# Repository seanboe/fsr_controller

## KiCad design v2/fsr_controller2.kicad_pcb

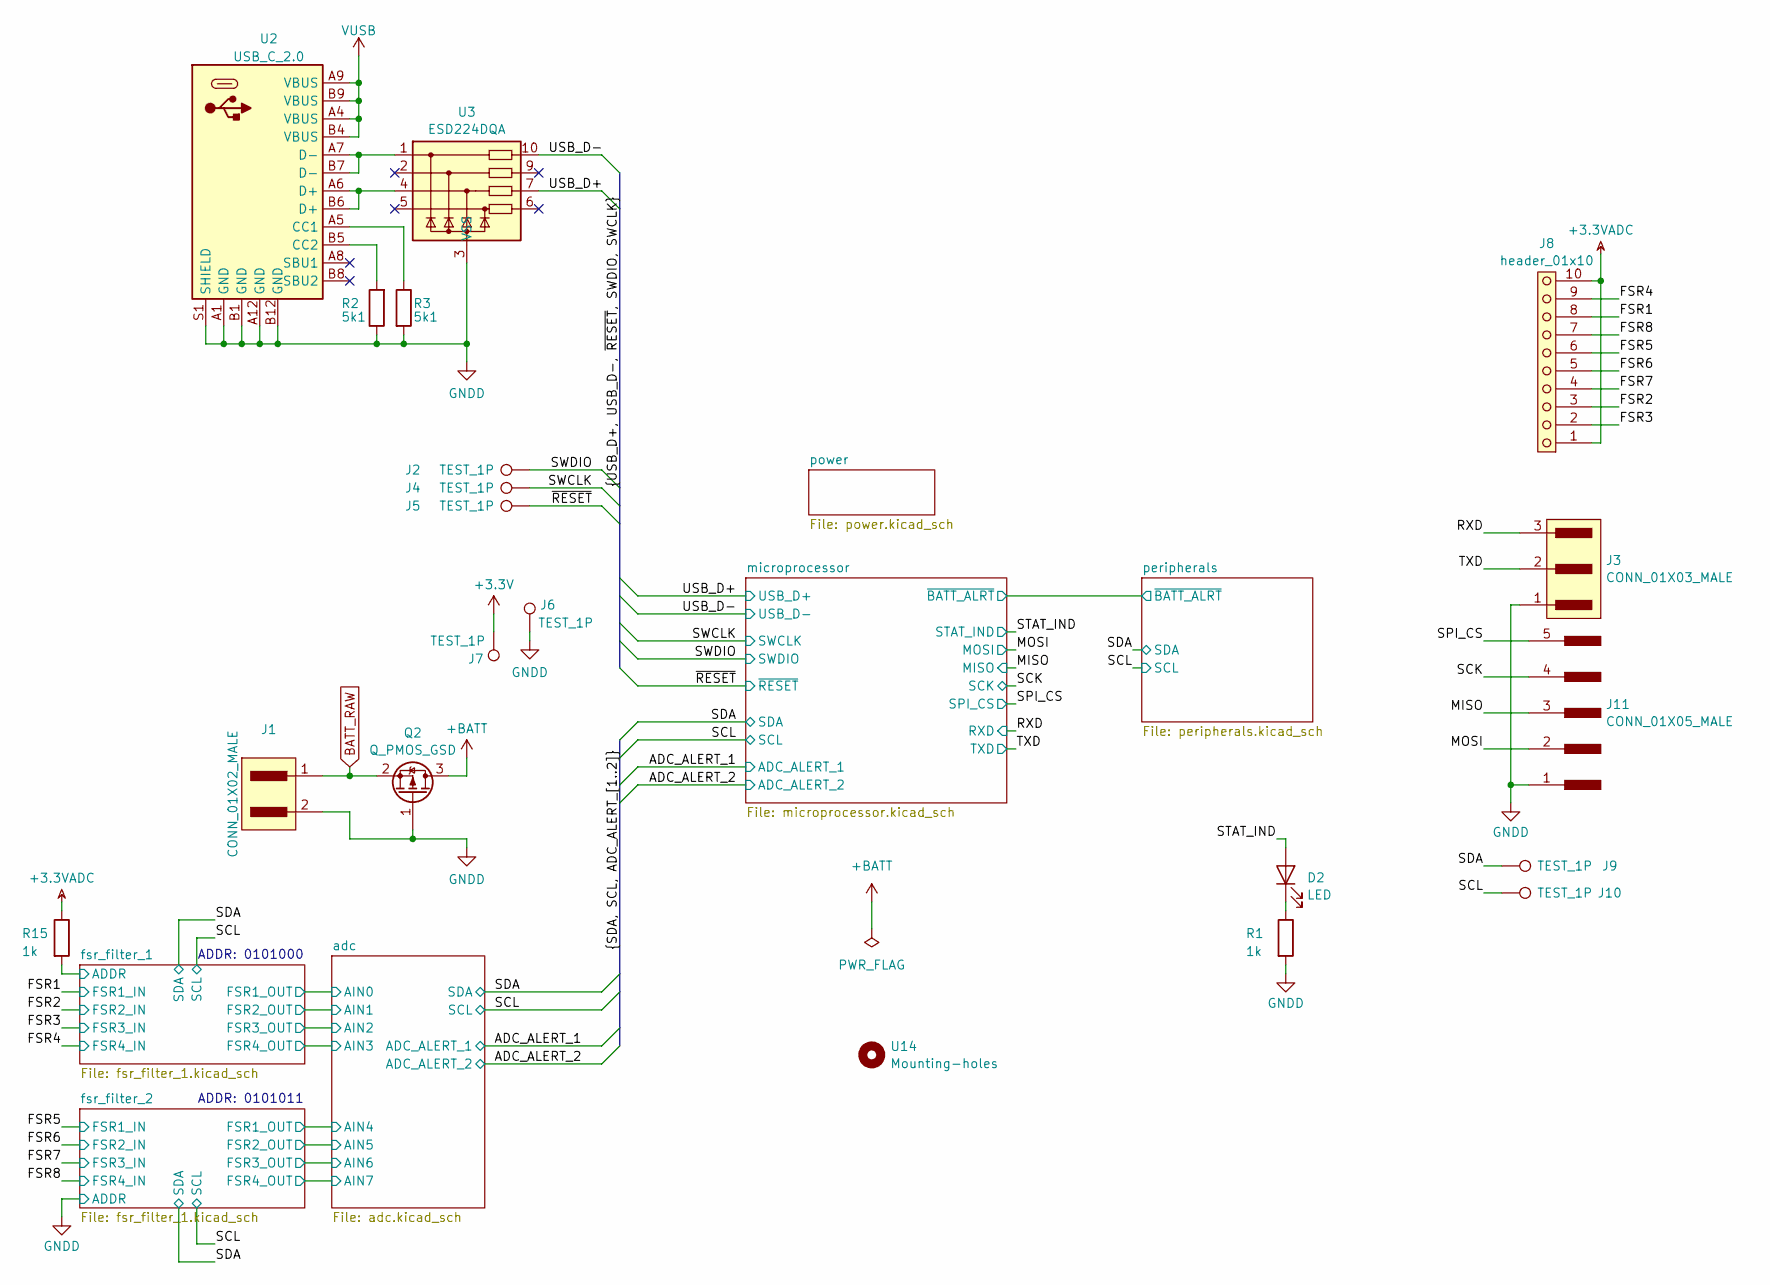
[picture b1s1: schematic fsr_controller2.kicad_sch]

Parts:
D2: LED; D_0603; MPN C94869
J1: CONN_01X02_MALE; JST_PH_S2B-PH-SM4-TB_1x02-1MP_P2.00mm_Horizontal; MPN C295747
J2, J4, J5, J6, J7, J9, J10: TEST_1P; test_point_1.0mm_square
J3: CONN_01X03_MALE; JST_BM03B_GHS_TB; MPN C514175
J8: header_01x10; fsr_connector
J11: CONN_01X05_MALE; JST_SM05B; MPN C189896
Q2: Q_PMOS_GSD; SOT-23; MPN C727156
R1, R15: 1k; R_1608_603_B; MPN C2984405
R2, R3: 5k1; R_1608_603_B; MPN C23186
U2: USB_C_2.0; USB_C_XKB_U262-16XN-4BVC11; MPN C165948
U3: ESD224DQA; Diodes_UDFN-10_1.0x2.5mm_P0.5mm
U14: Mounting-holes; plated_hole_2.0x2.5mm

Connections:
+3.3V: J7.1; also elsewhere on the board
+3.3VADC: J8.1, J8.10, R15.1; also elsewhere on the board
+BATT: Q2.3 (D); also elsewhere on the board
/FSR1: J8.8; also elsewhere on the board
/FSR2: J8.3; also elsewhere on the board
/FSR3: J8.2; also elsewhere on the board
/FSR4: J8.9; also elsewhere on the board
/FSR5: J8.6; also elsewhere on the board
/FSR6: J8.5; also elsewhere on the board
/FSR7: J8.4; also elsewhere on the board
/FSR8: J8.7; also elsewhere on the board
/MISO: J11.3; also elsewhere on the board
/MOSI: J11.2; also elsewhere on the board
/RXD: J3.3; also elsewhere on the board
/SCK: J11.4; also elsewhere on the board
/SCL: J10.1; also elsewhere on the board
/SDA: J9.1; also elsewhere on the board
/SPI_CS: J11.5; also elsewhere on the board
/STAT_IND: D2.2 (A); also elsewhere on the board
/SWCLK: J4.1; also elsewhere on the board
/SWDIO: J2.1; also elsewhere on the board
/TXD: J3.2; also elsewhere on the board
/USB_D+: U3.7; also elsewhere on the board
/USB_D-: U3.10; also elsewhere on the board
/fsr_filter_1/ADDR: R15.2; also elsewhere on the board
/~RESET: J5.1; also elsewhere on the board
BATT_RAW: J1.1, Q2.2 (S); also elsewhere on the board
GNDD: J1.2, J3.1, J6.1, J11.1, Q2.1 (G), R1.2, R2.1, R3.2, U2.A1 (GND), U2.A12 (GND), U2.B1 (GND), U2.B12 (GND), U2.S1 (SHIELD), U3.3 (VSS), U3.8 (VSS); also elsewhere on the board
unnamed: D2.1 (K), R1.1
unnamed: R3.1, U2.A5 (CC1)
unnamed: R2.2, U2.B5 (CC2)
unnamed: U2.A6 (D+), U2.B6 (D+), U3.4
unnamed: U2.A7 (D-), U2.B7 (D-), U3.1
VUSB: U2.A4 (VBUS), U2.A9 (VBUS), U2.B4 (VBUS), U2.B9 (VBUS); also elsewhere on the board

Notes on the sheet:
ADDR: 0101011
ADDR: 0101000

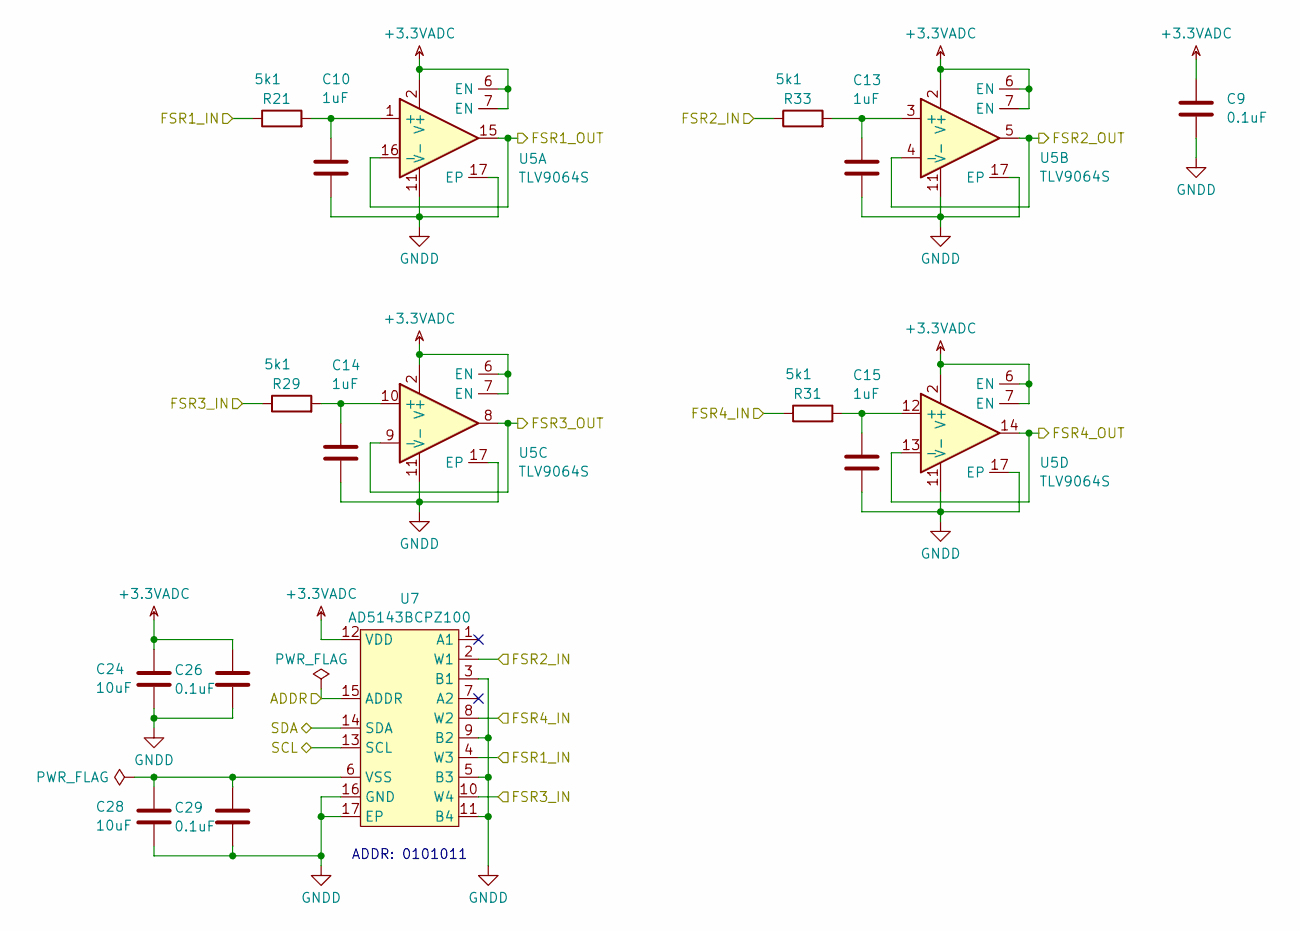
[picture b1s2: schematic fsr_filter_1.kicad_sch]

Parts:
C9, C26, C29: 0.1uF; C_1608_603_B; MPN C2909630
C10, C13, C14, C15: 1uF; C_1608_603_B; MPN C2918499
C24, C28: 10uF; C_1608_603_B; MPN C2909630
R21, R29, R31, R33: 5k1; R_1608_603_B; MPN C23186
U5: TLV9064S; WQFN-16-1EP_3x3mm_P0.5mm_EP1.68x1.68mm; MPN DIGI
U7: AD5143BCPZ100; WQFN-16-1EP_3x3mm_P0.5mm_EP1.68x1.68mm

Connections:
+3.3VADC: C9.1, C24.1, C26.1, U5.2 (V+), U5.6 (EN), U5.7 (EN), U7.12 (VDD); also elsewhere on the board
/FSR1: R21.1, U7.4 (W3); also elsewhere on the board
/FSR2: R33.1, U7.2 (W1); also elsewhere on the board
/FSR3: R29.1, U7.10 (W4); also elsewhere on the board
/FSR4: R31.1, U7.8 (W2); also elsewhere on the board
/SCL: U7.13 (SCL); also elsewhere on the board
/SDA: U7.14 (SDA); also elsewhere on the board
/adc/AIN0: U5.15, U5.16 (-); also elsewhere on the board
/adc/AIN1: U5.4 (-), U5.5; also elsewhere on the board
/adc/AIN2: U5.8, U5.9 (-); also elsewhere on the board
/adc/AIN3: U5.13 (-), U5.14; also elsewhere on the board
/fsr_filter_1/ADDR: U7.15 (ADDR); also elsewhere on the board
GNDD: C9.2, C10.2, C13.2, C14.2, C15.2, C24.2, C26.2, C28.2, C29.2, U5.11 (V-), U5.17 (EP), U7.3 (B1), U7.5 (B3), U7.9 (B2), U7.11 (B4), U7.16 (GND), U7.17 (EP); also elsewhere on the board
unnamed: C10.1, R21.2, U5.1 (+)
unnamed: C13.1, R33.2, U5.3 (+)
unnamed: C14.1, R29.2, U5.10 (+)
unnamed: C15.1, R31.2, U5.12 (+)
unnamed: C28.1, C29.1, U7.6 (VSS)

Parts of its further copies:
C3, C4: 10uF; C_1608_603_B; MPN C2909630
C12, C16, C25: 0.1uF; C_1608_603_B; MPN C2909630
C17, C18, C19, C22: 1uF; C_1608_603_B; MPN C2918499
R11, R12, R13, R14: 5k1; R_1608_603_B; MPN C23186
U12: TLV9064S; WQFN-16-1EP_3x3mm_P0.5mm_EP1.68x1.68mm; MPN DIGI
U13: AD5143BCPZ100; WQFN-16-1EP_3x3mm_P0.5mm_EP1.68x1.68mm

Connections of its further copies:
+3.3VADC: C3.1, C12.1, C25.1, U12.2 (V+), U12.6 (EN), U12.7 (EN), U13.12 (VDD); also elsewhere on the board
/FSR5: R11.1, U13.4 (W3); also elsewhere on the board
/FSR6: R13.1, U13.2 (W1); also elsewhere on the board
/FSR7: R12.1, U13.10 (W4); also elsewhere on the board
/FSR8: R14.1, U13.8 (W2); also elsewhere on the board
/SCL: U13.13 (SCL); also elsewhere on the board
/SDA: U13.14 (SDA); also elsewhere on the board
/adc/AIN4: U12.15, U12.16 (-); also elsewhere on the board
/adc/AIN5: U12.4 (-), U12.5; also elsewhere on the board
/adc/AIN6: U12.8, U12.9 (-); also elsewhere on the board
/adc/AIN7: U12.13 (-), U12.14; also elsewhere on the board
GNDD: C3.2, C4.2, C12.2, C16.2, C17.2, C18.2, C19.2, C22.2, C25.2, U12.11 (V-), U12.17 (EP), U13.3 (B1), U13.5 (B3), U13.9 (B2), U13.11 (B4), U13.15 (ADDR), U13.16 (GND), U13.17 (EP); also elsewhere on the board
unnamed: C17.1, R11.2, U12.1 (+)
unnamed: C19.1, R13.2, U12.3 (+)
unnamed: C18.1, R12.2, U12.10 (+)
unnamed: C22.1, R14.2, U12.12 (+)
unnamed: C4.1, C16.1, U13.6 (VSS)

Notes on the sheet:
ADDR: 0101011

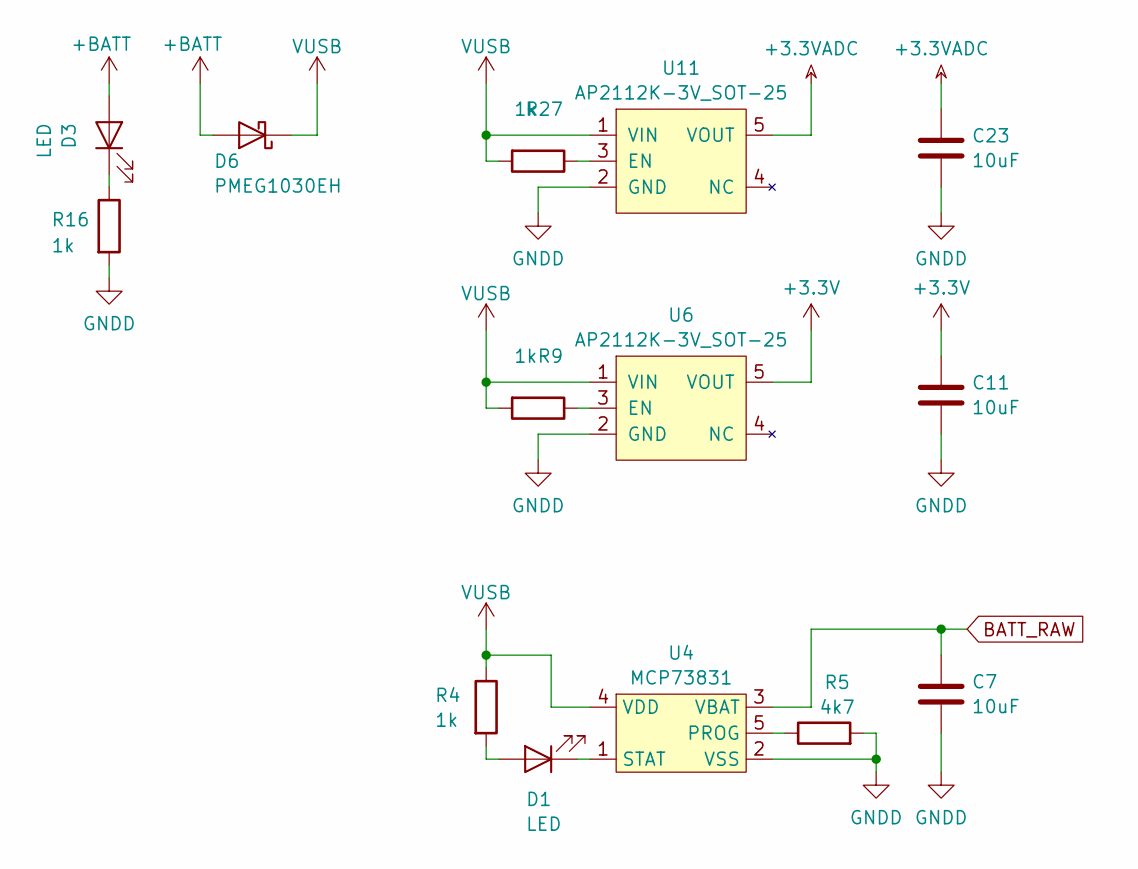
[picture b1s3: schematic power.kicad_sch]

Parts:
C7, C11, C23: 10uF; C_1608_603_B; MPN C2909630
D1, D3: LED; D_0603; MPN C94869
D6: PMEG1030EH; D_SOD-123F; MPN DIGI
R4, R9, R16, R27: 1k; R_1608_603_B; MPN C2984405
R5: 4k7; R_1608_603_B; MPN C2984421
U4: MCP73831; SOT-23-5; MPN C424093
U6, U11: AP2112K-3V_SOT-25; SOT-23-5; MPN C51118

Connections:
+3.3V: C11.1, U6.5 (VOUT); also elsewhere on the board
+3.3VADC: C23.1, U11.5 (VOUT); also elsewhere on the board
+BATT: D3.2 (A), D6.2 (A); also elsewhere on the board
BATT_RAW: C7.1, U4.3 (VBAT); also elsewhere on the board
GNDD: C7.2, C11.2, C23.2, R5.2, R16.2, U4.2 (VSS), U6.2 (GND), U11.2 (GND); also elsewhere on the board
unnamed: D1.2 (A), R4.2
unnamed: D1.1 (K), U4.1 (STAT)
unnamed: D3.1 (K), R16.1
unnamed: R5.1, U4.5 (PROG)
unnamed: R9.1, U6.3 (EN)
unnamed: R27.1, U11.3 (EN)
VUSB: D6.1 (K), R4.1, R9.2, R27.2, U4.4 (VDD), U6.1 (VIN), U11.1 (VIN); also elsewhere on the board

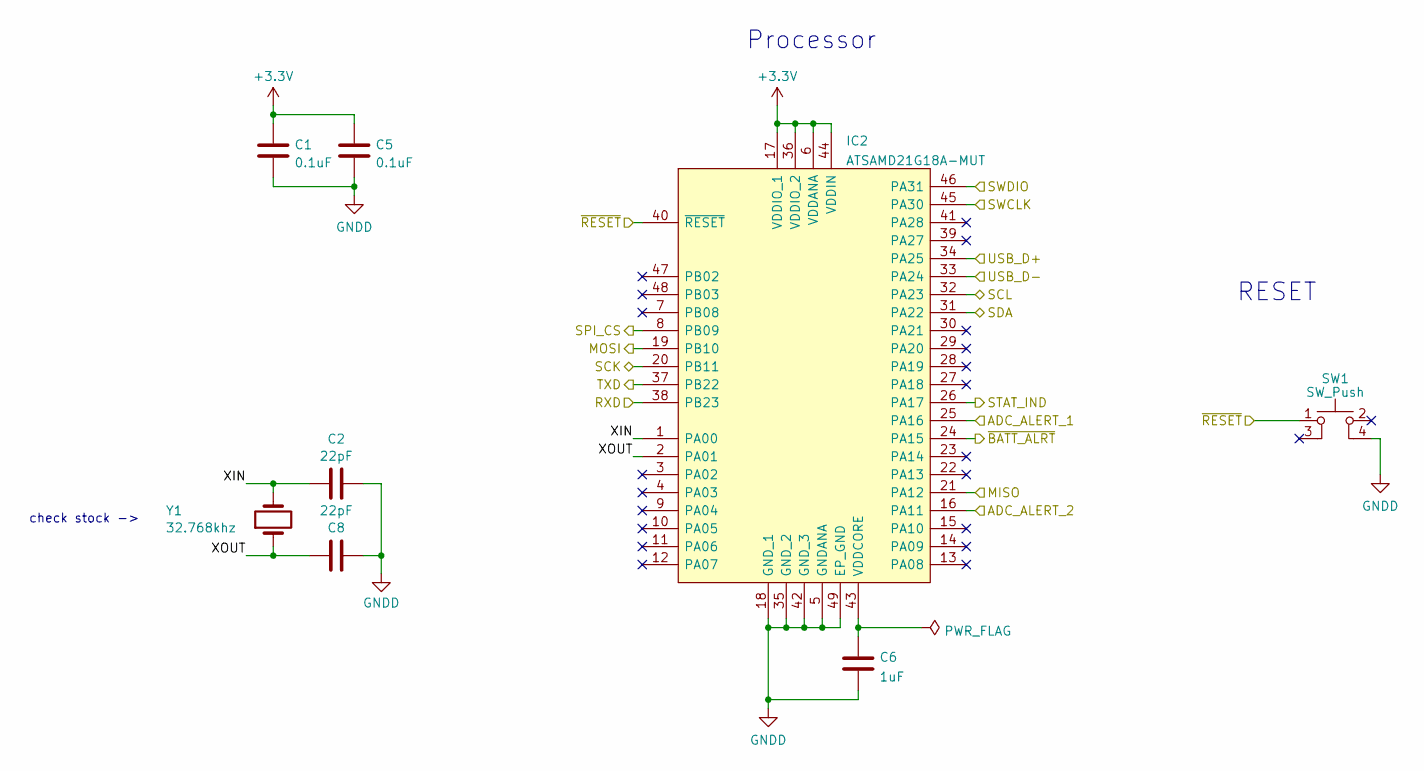
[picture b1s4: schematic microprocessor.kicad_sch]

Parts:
C1, C5: 0.1uF; C_1608_603_B; MPN C2909630
C2, C8: 22pF; C_1005_402_B; MPN C173271
C6: 1uF; C_1608_603_B; MPN C2918499
IC2: ATSAMD21G18A-MUT; QFN50P700X700X90-49N-D; MPN DIGI
SW1: SW_Push; TL3365AF180QG; MPN C2886926
Y1: 32.768khz; 2-smd

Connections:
+3.3V: C1.2, C5.2, IC2.6 (VDDANA), IC2.17 (VDDIO_1), IC2.36 (VDDIO_2), IC2.44 (VDDIN); also elsewhere on the board
/ADC_ALERT_1: IC2.25 (PA16); also elsewhere on the board
/ADC_ALERT_2: IC2.16 (PA11); also elsewhere on the board
/MISO: IC2.21 (PA12); also elsewhere on the board
/MOSI: IC2.19 (PB10); also elsewhere on the board
/RXD: IC2.38 (PB23); also elsewhere on the board
/SCK: IC2.20 (PB11); also elsewhere on the board
/SCL: IC2.32 (PA23); also elsewhere on the board
/SDA: IC2.31 (PA22); also elsewhere on the board
/SPI_CS: IC2.8 (PB09); also elsewhere on the board
/STAT_IND: IC2.26 (PA17); also elsewhere on the board
/SWCLK: IC2.45 (PA30); also elsewhere on the board
/SWDIO: IC2.46 (PA31); also elsewhere on the board
/TXD: IC2.37 (PB22); also elsewhere on the board
/USB_D+: IC2.34 (PA25); also elsewhere on the board
/USB_D-: IC2.33 (PA24); also elsewhere on the board
/microprocessor/XIN: C2.2, IC2.1 (PA00), Y1.2
/microprocessor/XOUT: C8.2, IC2.2 (PA01), Y1.1
/peripherals/~ALRT: IC2.24 (PA15); also elsewhere on the board
/~RESET: IC2.40 (~RESET), SW1.1; also elsewhere on the board
GNDD: C1.1, C2.1, C5.1, C6.2, C8.1, IC2.5 (GNDANA), IC2.18 (GND_1), IC2.35 (GND_2), IC2.42 (GND_3), IC2.49 (EP_GND), SW1.4; also elsewhere on the board
unnamed: C6.1, IC2.43 (VDDCORE)

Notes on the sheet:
check stock ->
RESET
Processor

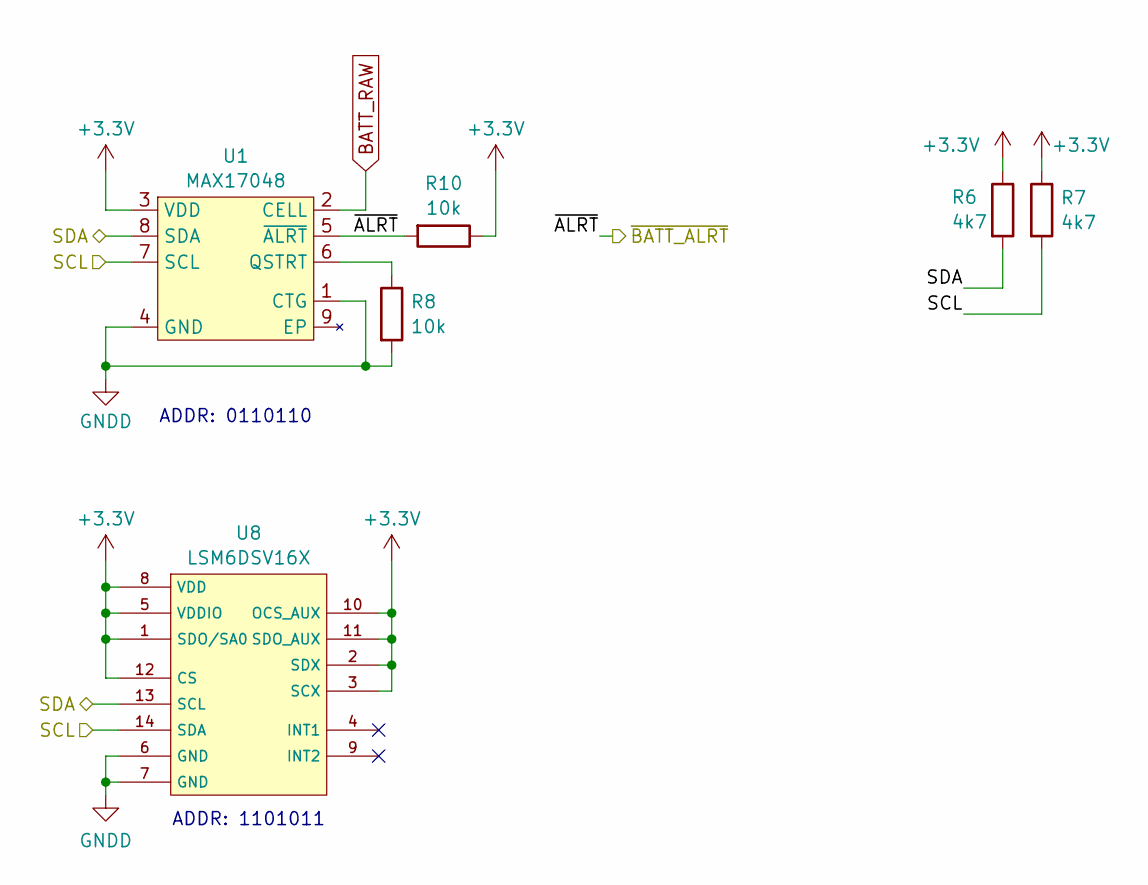
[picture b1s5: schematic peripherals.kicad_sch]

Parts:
R6, R7: 4k7; R_1608_603_B; MPN C2984421
R8, R10: 10k; R_1608_603_B; MPN C5123581
U1: MAX17048; DFN-8-1EP_2x2mm_P0.5mm_EP0.9x1.5mm; MPN C2682616
U8: LSM6DSV16X; PQFN50P250X300X86-14N; MPN DIGI

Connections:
+3.3V: R6.1, R7.1, R10.1, U1.3 (VDD), U8.1 (SDO/SA0), U8.2 (SDX), U8.3 (SCX), U8.5 (VDDIO), U8.8 (VDD), U8.10 (OCS_AUX), U8.11 (SDO_AUX), U8.12 (CS); also elsewhere on the board
/SCL: R7.2, U1.7 (SCL), U8.14 (SDA); also elsewhere on the board
/SDA: R6.2, U1.8 (SDA), U8.13 (SCL); also elsewhere on the board
/peripherals/~ALRT: R10.2, U1.5 (~ALRT); also elsewhere on the board
BATT_RAW: U1.2 (CELL); also elsewhere on the board
GNDD: R8.2, U1.1 (CTG), U1.4 (GND), U8.6 (GND), U8.7 (GND); also elsewhere on the board
unnamed: R8.1, U1.6 (QSTRT)

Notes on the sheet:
ADDR: 1101011
ADDR: 0110110

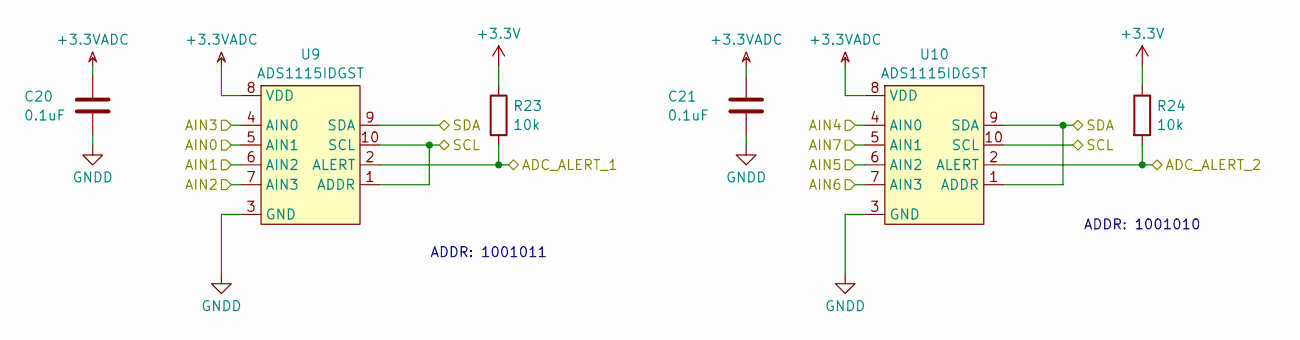
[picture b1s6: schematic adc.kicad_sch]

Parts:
C20, C21: 0.1uF; C_1608_603_B; MPN C2909630
R23, R24: 10k; R_1608_603_B; MPN C5123581
U9, U10: ADS1115IDGST; VSSOP-10_3x3mm_P0.5mm

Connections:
+3.3V: R23.1, R24.1; also elsewhere on the board
+3.3VADC: C20.1, C21.1, U9.8 (VDD), U10.8 (VDD); also elsewhere on the board
/ADC_ALERT_1: R23.2, U9.2 (ALERT); also elsewhere on the board
/ADC_ALERT_2: R24.2, U10.2 (ALERT); also elsewhere on the board
/SCL: U9.1 (ADDR), U9.10 (SCL), U10.10 (SCL); also elsewhere on the board
/SDA: U9.9 (SDA), U10.1 (ADDR), U10.9 (SDA); also elsewhere on the board
/adc/AIN0: U9.5 (AIN1); also elsewhere on the board
/adc/AIN1: U9.6 (AIN2); also elsewhere on the board
/adc/AIN2: U9.7 (AIN3); also elsewhere on the board
/adc/AIN3: U9.4 (AIN0); also elsewhere on the board
/adc/AIN4: U10.4 (AIN0); also elsewhere on the board
/adc/AIN5: U10.6 (AIN2); also elsewhere on the board
/adc/AIN6: U10.7 (AIN3); also elsewhere on the board
/adc/AIN7: U10.5 (AIN1); also elsewhere on the board
GNDD: C20.2, C21.2, U9.3 (GND), U10.3 (GND); also elsewhere on the board

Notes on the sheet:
ADDR: 1001010
ADDR: 1001011

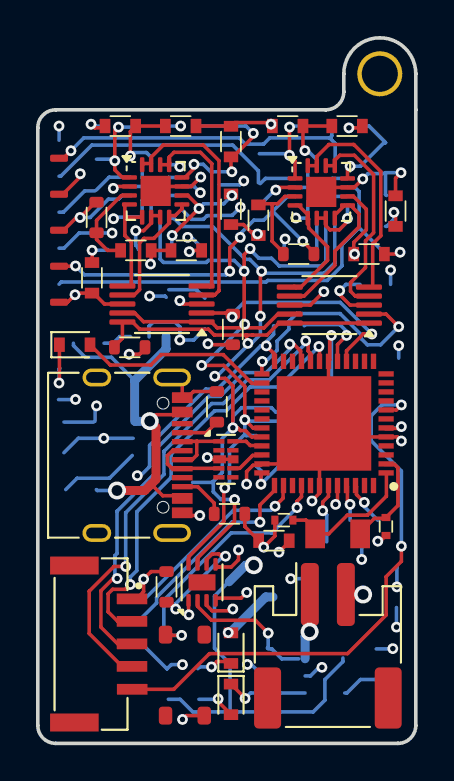
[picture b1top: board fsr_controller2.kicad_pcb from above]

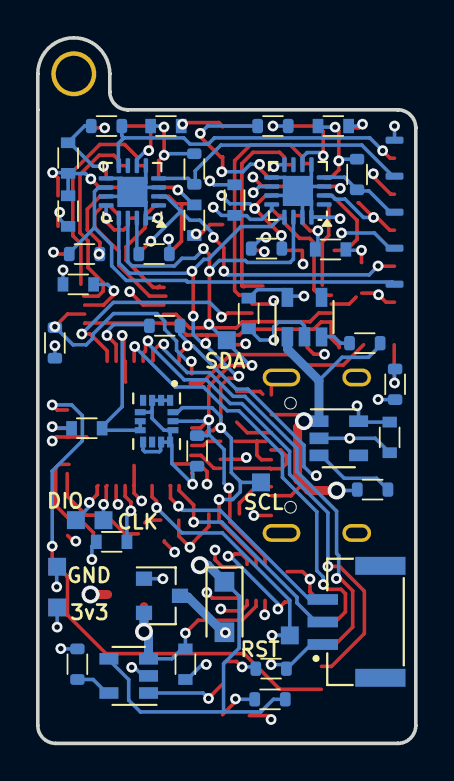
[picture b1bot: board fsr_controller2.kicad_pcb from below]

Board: 4 copper layers, 21.0 x 39.2 mm, 84 parts (45 on the bottom side), 65 nets.

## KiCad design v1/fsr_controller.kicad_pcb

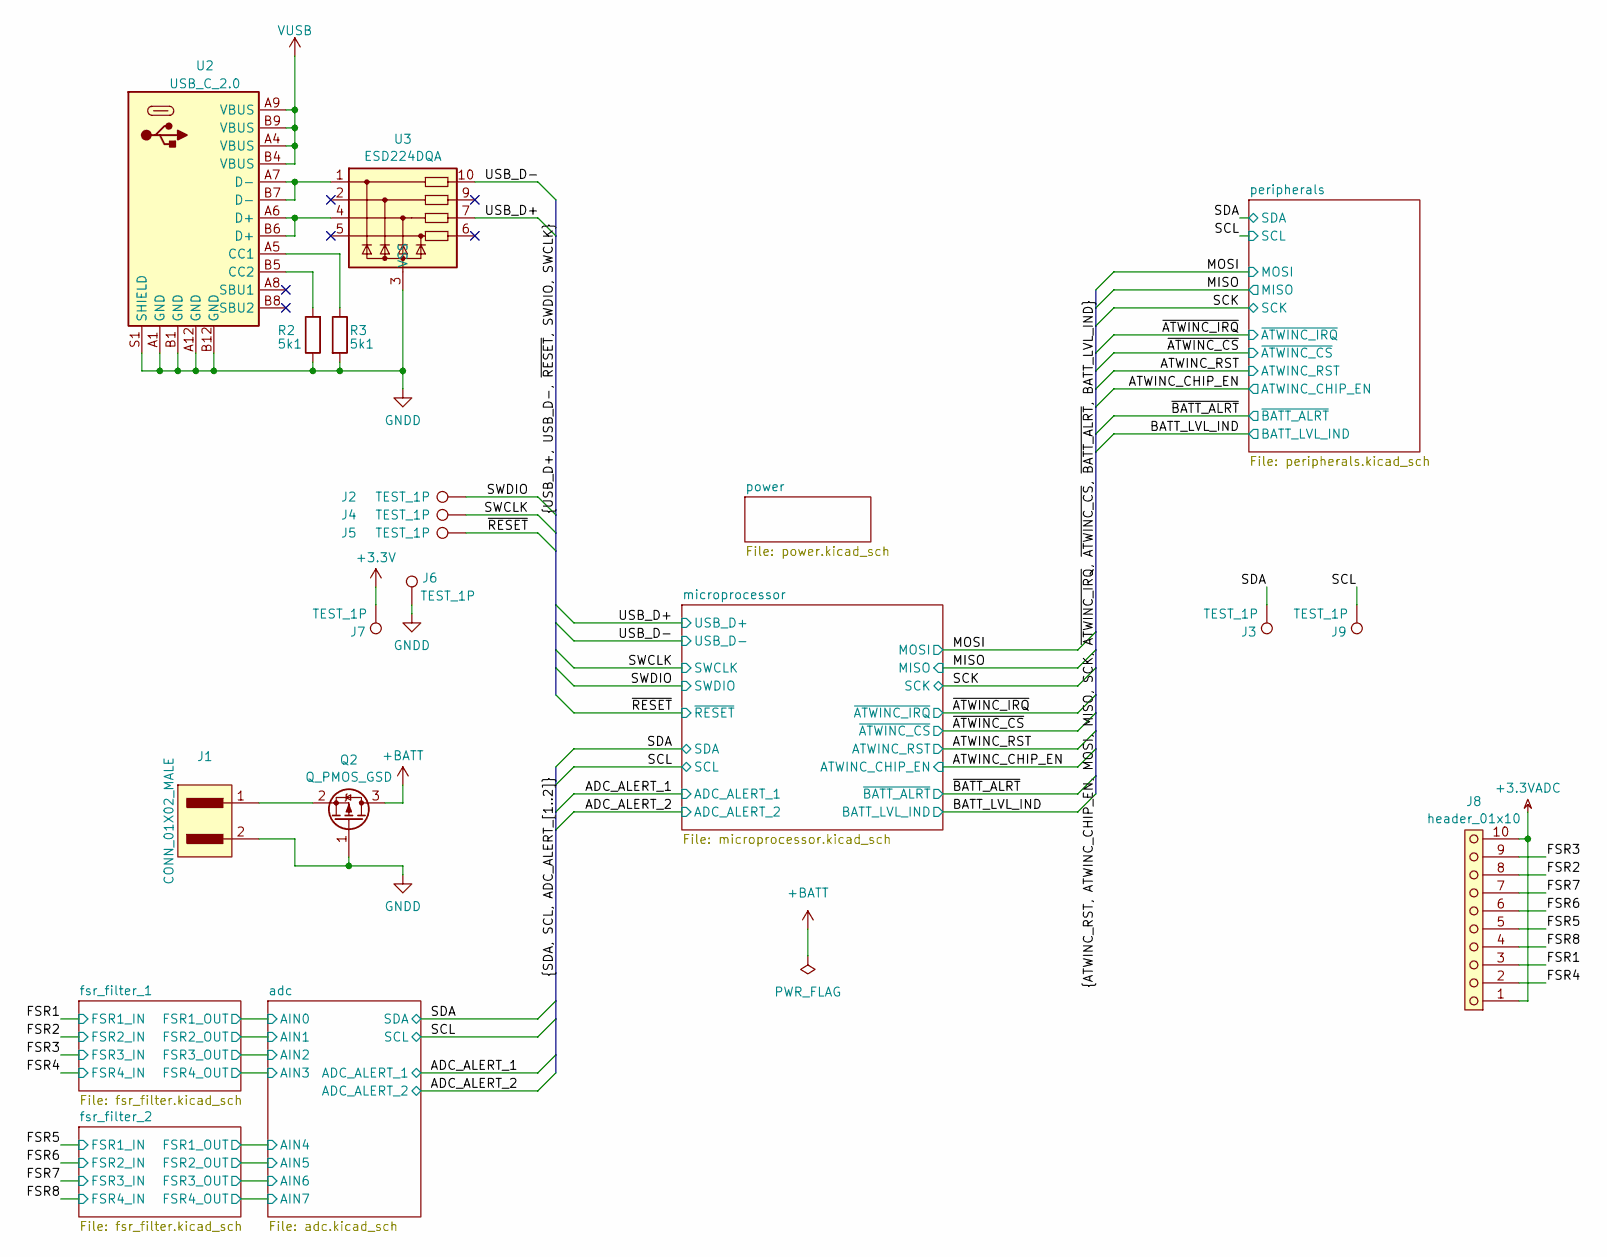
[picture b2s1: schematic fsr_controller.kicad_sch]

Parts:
J1: CONN_01X02_MALE; JST_PH_S2B-PH-SM4-TB_1x02-1MP_P2.00mm_Horizontal
J2, J3, J4, J5, J6, J7, J9: TEST_1P; test_point_1.0mm_square
J8: header_01x10; fsr_connector
Q2: Q_PMOS_GSD; SOT-23
R2, R3: 5k1; R_1608_603_B
U2: USB_C_2.0; USB_C_XKB_U262-16XN-4BVC11
U3: ESD224DQA; Diodes_UDFN-10_1.0x2.5mm_P0.5mm

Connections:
+3.3V: J7.1; also elsewhere on the board
+3.3VADC: J8.1, J8.10; also elsewhere on the board
+BATT: Q2.3 (D); also elsewhere on the board
/FSR1: J8.3; also elsewhere on the board
/FSR2: J8.8; also elsewhere on the board
/FSR3: J8.9; also elsewhere on the board
/FSR4: J8.2; also elsewhere on the board
/FSR5: J8.5; also elsewhere on the board
/FSR6: J8.6; also elsewhere on the board
/FSR7: J8.7; also elsewhere on the board
/FSR8: J8.4; also elsewhere on the board
/SCL: J9.1; also elsewhere on the board
/SDA: J3.1; also elsewhere on the board
/SWCLK: J4.1; also elsewhere on the board
/SWDIO: J2.1; also elsewhere on the board
/USB_D+: U3.7; also elsewhere on the board
/USB_D-: U3.10; also elsewhere on the board
/~RESET: J5.1; also elsewhere on the board
GNDD: J1.2, J6.1, Q2.1 (G), R2.1, R3.2, U2.A1 (GND), U2.A12 (GND), U2.B1 (GND), U2.B12 (GND), U2.S1 (SHIELD), U3.3 (VSS), U3.8 (VSS); also elsewhere on the board
unnamed: J1.1, Q2.2 (S)
unnamed: R3.1, U2.A5 (CC1)
unnamed: R2.2, U2.B5 (CC2)
unnamed: U2.A6 (D+), U2.B6 (D+), U3.4
unnamed: U2.A7 (D-), U2.B7 (D-), U3.1
VUSB: U2.A4 (VBUS), U2.A9 (VBUS), U2.B4 (VBUS), U2.B9 (VBUS); also elsewhere on the board

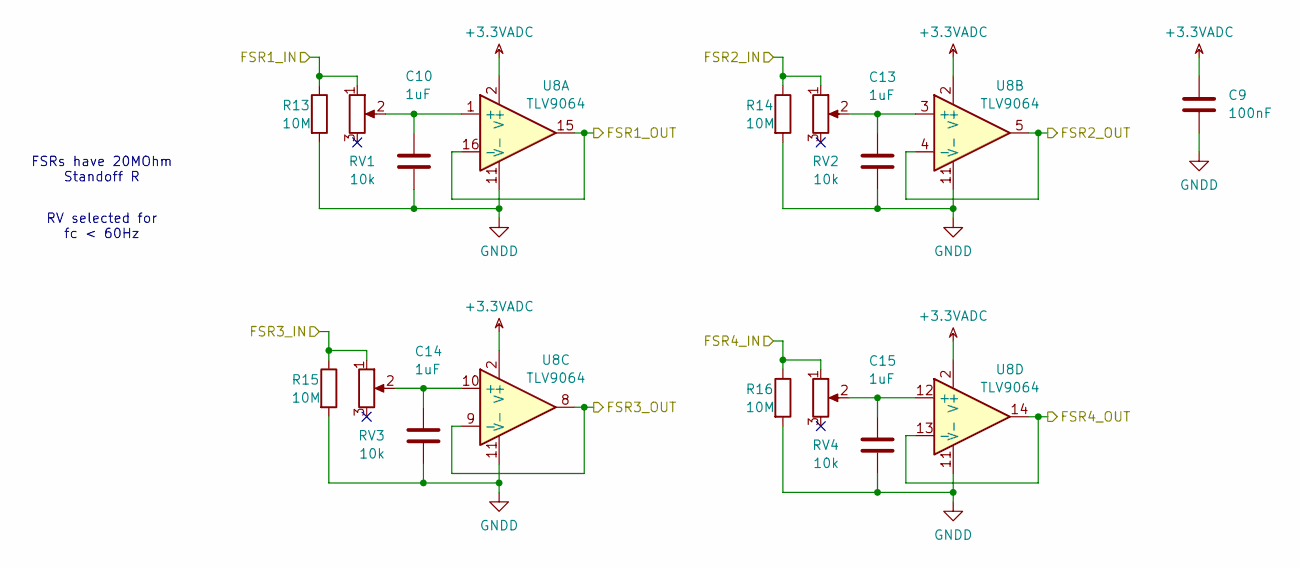
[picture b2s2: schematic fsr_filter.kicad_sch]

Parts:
C9: 100nF; C_1608_603_B
C10, C13, C14, C15: 1uF; C_1608_603_B
R13, R14, R15, R16: 10M; R_1608_603_B
RV1, RV2, RV3, RV4: 10k; potentiometer
U8: TLV9064; WQFN-16-1EP_3x3mm_P0.5mm_EP1.68x1.68mm

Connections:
+3.3VADC: C9.1, U8.2 (V+); also elsewhere on the board
/FSR1: R13.1, RV1.1; also elsewhere on the board
/FSR2: R14.1, RV2.1; also elsewhere on the board
/FSR3: R15.1, RV3.1; also elsewhere on the board
/FSR4: R16.1, RV4.1; also elsewhere on the board
/adc/AIN4: U8.15, U8.16 (-); also elsewhere on the board
/adc/AIN5: U8.4 (-), U8.5; also elsewhere on the board
/adc/AIN6: U8.8, U8.9 (-); also elsewhere on the board
/adc/AIN7: U8.13 (-), U8.14; also elsewhere on the board
GNDD: C9.2, C10.2, C13.2, C14.2, C15.2, R13.2, R14.2, R15.2, R16.2, U8.11 (V-); also elsewhere on the board

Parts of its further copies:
C16, C17, C18, C19: 1uF; C_1608_603_B
C22: 100nF; C_1608_603_B
R17, R18, R19, R20: 10M; R_1608_603_B
RV5, RV6, RV7, RV8: 10k; potentiometer
U7: TLV9064; WQFN-16-1EP_3x3mm_P0.5mm_EP1.68x1.68mm

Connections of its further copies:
+3.3VADC: C22.1, U7.2 (V+); also elsewhere on the board
/FSR5: R17.1, RV5.1; also elsewhere on the board
/FSR6: R19.1, RV7.1; also elsewhere on the board
/FSR7: R18.1, RV6.1; also elsewhere on the board
/FSR8: R20.1, RV8.1; also elsewhere on the board
/adc/AIN0: U7.15, U7.16 (-); also elsewhere on the board
/adc/AIN1: U7.4 (-), U7.5; also elsewhere on the board
/adc/AIN2: U7.8, U7.9 (-); also elsewhere on the board
/adc/AIN3: U7.13 (-), U7.14; also elsewhere on the board
GNDD: C16.2, C17.2, C18.2, C19.2, C22.2, R17.2, R18.2, R19.2, R20.2, U7.11 (V-); also elsewhere on the board

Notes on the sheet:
FSRs have 20MOhm Standoff R
RV selected for fc < 60Hz

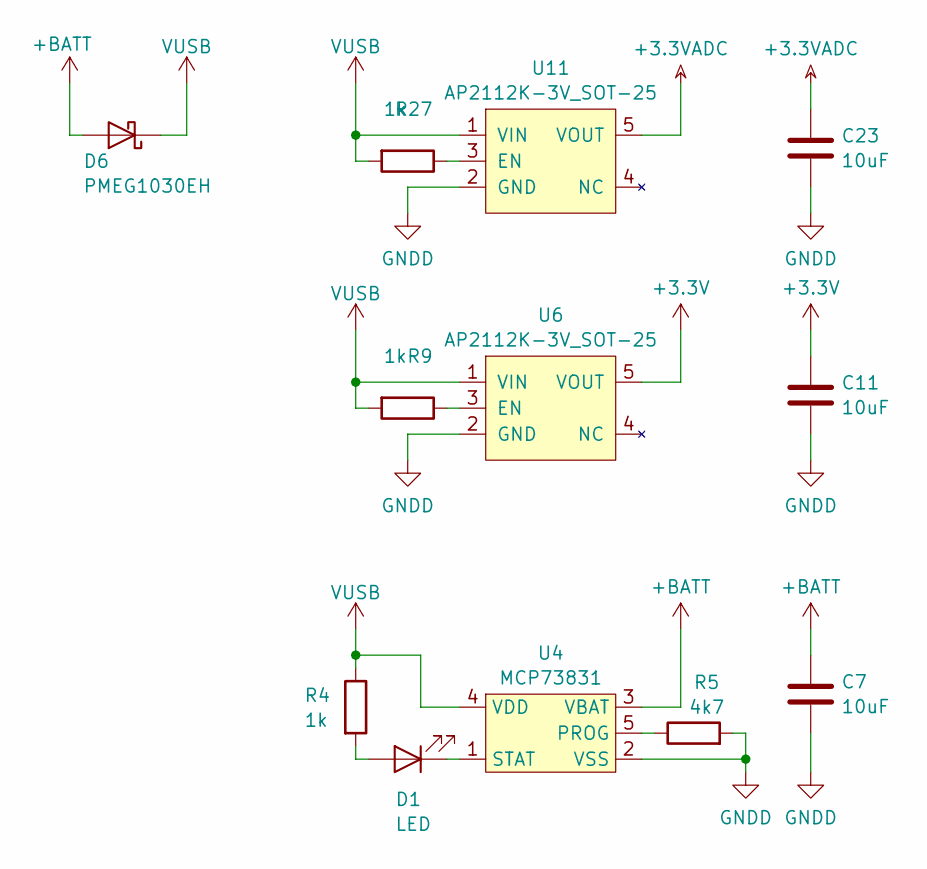
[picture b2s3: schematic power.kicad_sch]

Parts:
C7, C11, C23: 10uF; C_1608_603_B
D1: LED; D_0603
D6: PMEG1030EH; D_SOD-123F
R4, R9, R27: 1k; R_1608_603_B
R5: 4k7; R_1608_603_B
U4: MCP73831; SOT-23-5
U6, U11: AP2112K-3V_SOT-25; SOT-23-5

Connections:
+3.3V: C11.1, U6.5 (VOUT); also elsewhere on the board
+3.3VADC: C23.1, U11.5 (VOUT); also elsewhere on the board
+BATT: C7.1, D6.2 (A), U4.3 (VBAT); also elsewhere on the board
GNDD: C7.2, C11.2, C23.2, R5.2, U4.2 (VSS), U6.2 (GND), U11.2 (GND); also elsewhere on the board
unnamed: D1.2 (A), R4.2
unnamed: D1.1 (K), U4.1 (STAT)
unnamed: R5.1, U4.5 (PROG)
unnamed: R9.1, U6.3 (EN)
unnamed: R27.1, U11.3 (EN)
VUSB: D6.1 (K), R4.1, R9.2, R27.2, U4.4 (VDD), U6.1 (VIN), U11.1 (VIN); also elsewhere on the board

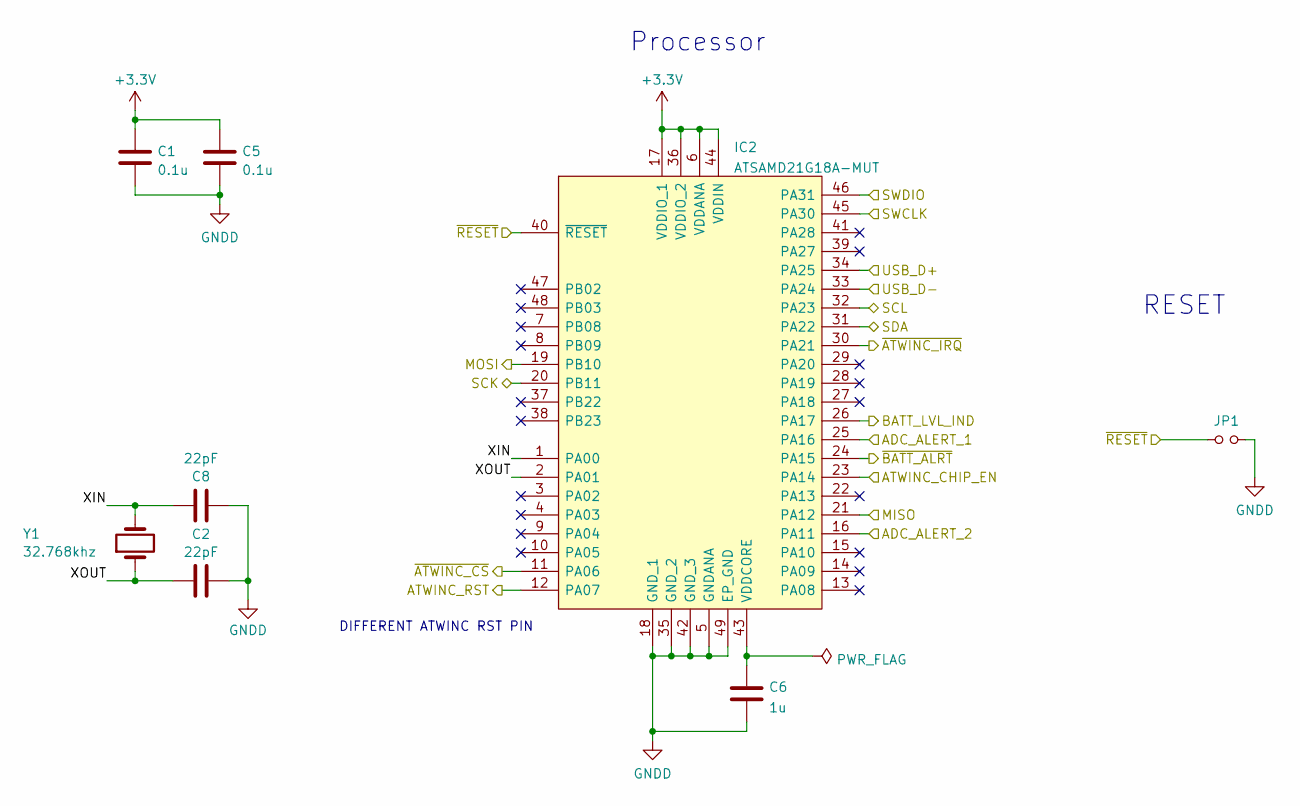
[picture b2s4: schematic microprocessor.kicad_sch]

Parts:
C1, C5: 0.1u; C_1608_603_B
C2, C8: 22pF; C_1005_402_B
C6: 1u; C_1608_603_B
IC2: ATSAMD21G18A-MUT; QFN50P700X700X90-49N-D
JP1: Jumper_NO_Small; SolderJumper-2_P1.3mm_Open_RoundedPad1.0x1.5mm
Y1: 32.768khz; 2-smd

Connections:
+3.3V: C1.2, C5.2, IC2.6 (VDDANA), IC2.17 (VDDIO_1), IC2.36 (VDDIO_2), IC2.44 (VDDIN); also elsewhere on the board
/ADC_ALERT_1: IC2.25 (PA16); also elsewhere on the board
/ADC_ALERT_2: IC2.16 (PA11); also elsewhere on the board
/ATWINC_CHIP_EN: IC2.23 (PA14); also elsewhere on the board
/ATWINC_RST: IC2.12 (PA07); also elsewhere on the board
/BATT_LVL_IND: IC2.26 (PA17); also elsewhere on the board
/MISO: IC2.21 (PA12); also elsewhere on the board
/MOSI: IC2.19 (PB10); also elsewhere on the board
/SCK: IC2.20 (PB11); also elsewhere on the board
/SCL: IC2.32 (PA23); also elsewhere on the board
/SDA: IC2.31 (PA22); also elsewhere on the board
/SWCLK: IC2.45 (PA30); also elsewhere on the board
/SWDIO: IC2.46 (PA31); also elsewhere on the board
/USB_D+: IC2.34 (PA25); also elsewhere on the board
/USB_D-: IC2.33 (PA24); also elsewhere on the board
/microprocessor/XIN: C8.2, IC2.1 (PA00), Y1.2
/microprocessor/XOUT: C2.2, IC2.2 (PA01), Y1.1
/~ATWINC_CS: IC2.11 (PA06); also elsewhere on the board
/~ATWINC_IRQ: IC2.30 (PA21); also elsewhere on the board
/~BATT_ALRT: IC2.24 (PA15); also elsewhere on the board
/~RESET: IC2.40 (~RESET), JP1.1; also elsewhere on the board
GNDD: C1.1, C2.1, C5.1, C6.2, C8.1, IC2.5 (GNDANA), IC2.18 (GND_1), IC2.35 (GND_2), IC2.42 (GND_3), IC2.49 (EP_GND), JP1.2; also elsewhere on the board
unnamed: C6.1, IC2.43 (VDDCORE)

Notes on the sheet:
RESET
DIFFERENT ATWINC RST PIN
Processor
